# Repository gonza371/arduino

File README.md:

# Arduino Shields

Proyecto destinado a la creacion de Shields de Arduino con displays de 7 segmentos bajo distintos metodos. Proyecto CIII

## 🚀 Características

- Multiplexado de 3 displays de 7 segmentos.
- Controlado desde Arduino UNO usando solo el puerto D.
- Circuito en KiCad con transistores NPN (2N2219).
- Ideal para aprender manejo de displays en proyectos embebidos.

## 🛠 Requisitos

- Arduino UNO
- 3 Displays de 7 segmentos catodo común (HDSP-7401)
- Transistores 2N2219
- Resistencias de 330Ω (segmentos) y 1kΩ (base de transistores)
- Fuente de 5V (puede ser la del Arduino)

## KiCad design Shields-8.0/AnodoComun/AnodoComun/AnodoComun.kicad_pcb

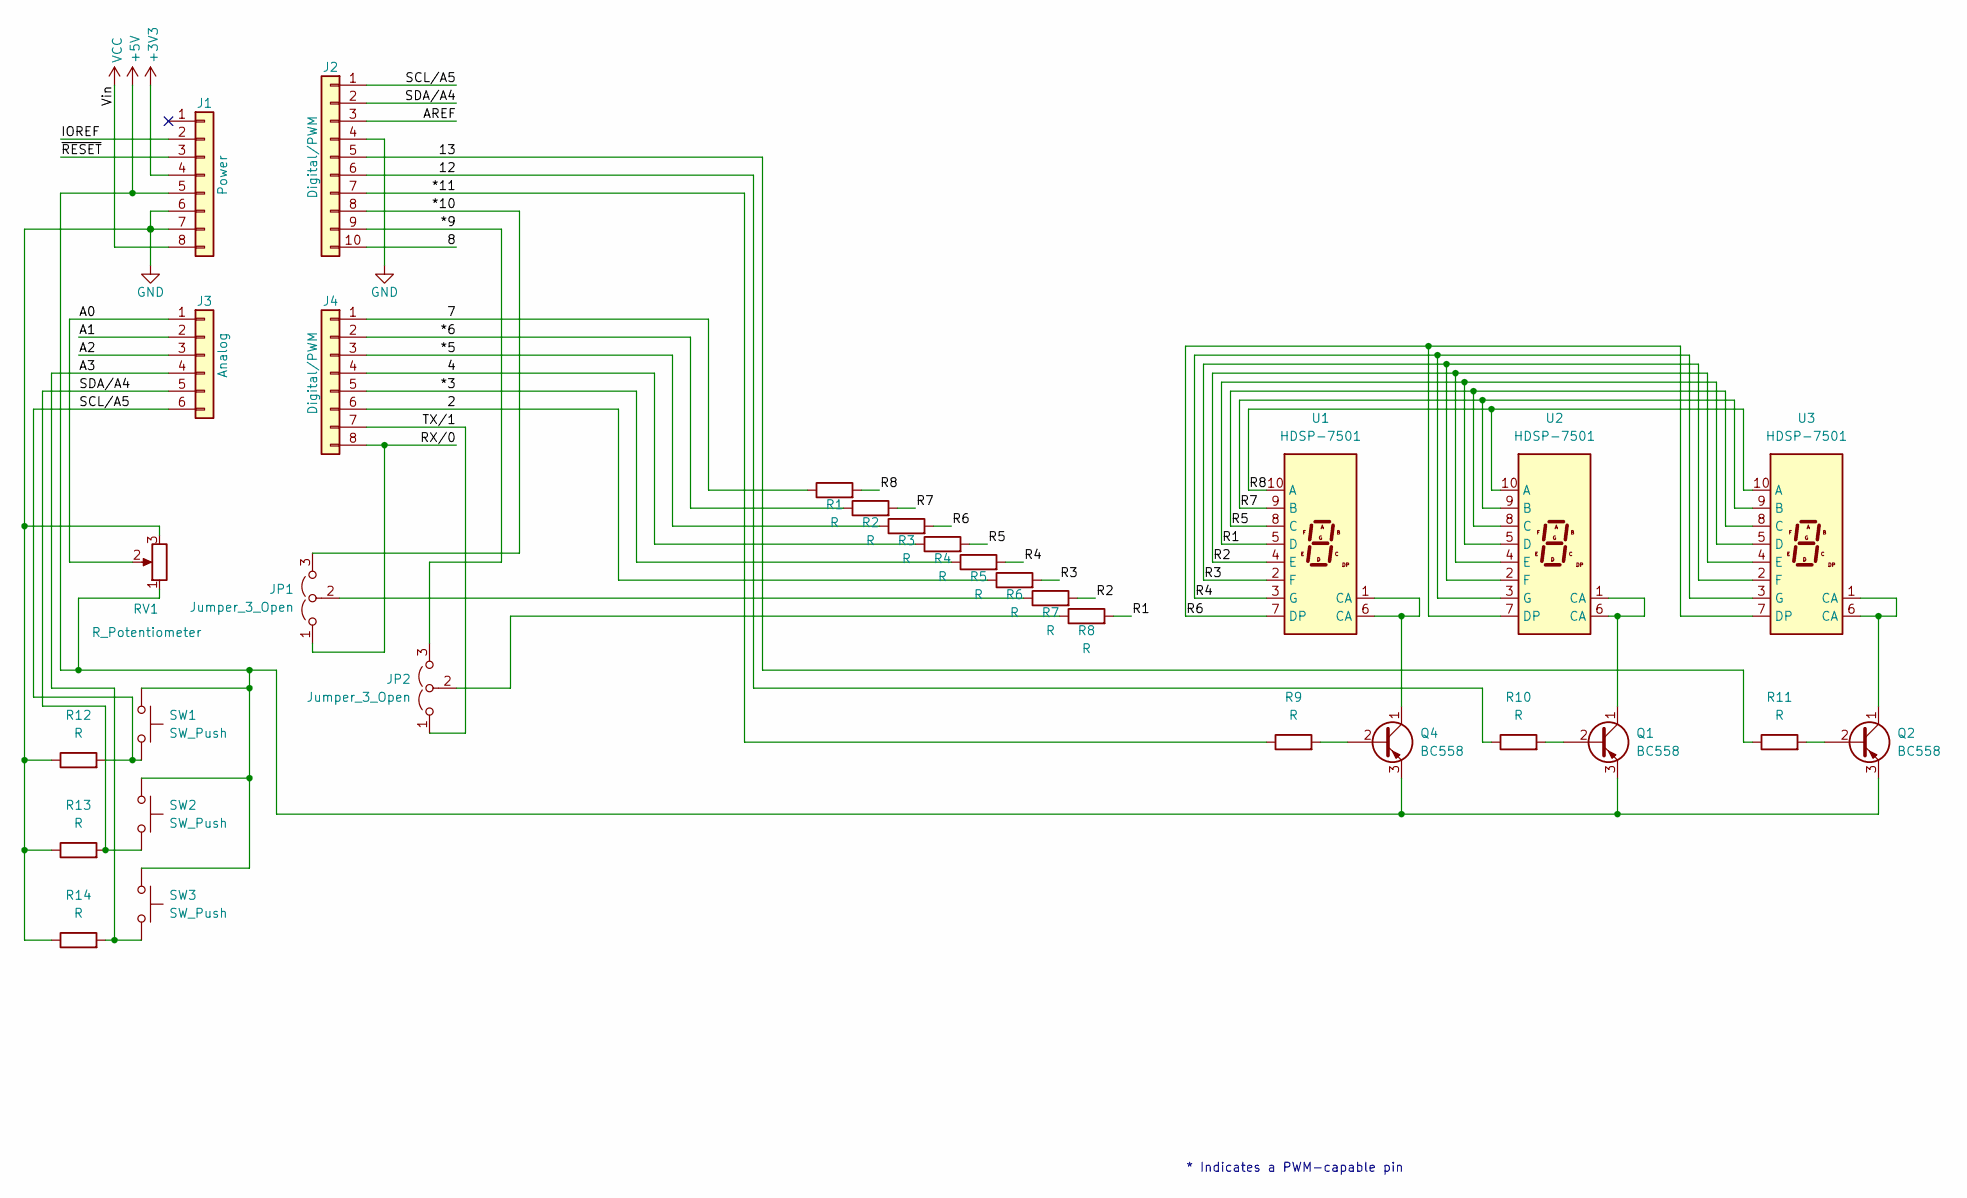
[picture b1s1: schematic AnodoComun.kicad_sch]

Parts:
J1: Power; PinSocket_1x08_P2.54mm_Vertical
J2: Digital/PWM; PinSocket_1x10_P2.54mm_Vertical
J3: Analog; PinSocket_1x06_P2.54mm_Vertical
J4: Digital/PWM; PinSocket_1x08_P2.54mm_Vertical
JP1, JP2: Jumper_3_Open; PinHeader_1x03_P2.54mm_Vertical
Q1, Q2, Q4: BC558; TO-92_Inline
R1, R2, R3, R4, R5, R6, R7, R8, R9, R10, R11, R12, R13, R14: R; R_Axial_DIN0207_L6.3mm_D2.5mm_P7.62mm_Horizontal
RV1: R_Potentiometer; Potentiometer_Alps_RK09K_Single_Horizontal
SW1, SW2, SW3: SW_Push; SW_PUSH_6mm_H4.3mm
U1, U2, U3: HDSP-7501; D1X8K_AC

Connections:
+3V3: J1.4
+5V: J1.5, Q1.3 (E), Q2.3 (E), Q4.3 (E), RV1.1, SW1.1, SW2.1, SW3.1
/2: J4.6, R6.1
/4: J4.4, R4.1
/7: J4.1, R1.1
/8: J2.10
/12: J2.6, R10.1
/13: J2.5, R11.1
/*3: J4.5, R5.1
/*5: J4.3, R3.1
/*6: J4.2, R2.1
/*9: J2.9, JP2.3 (B)
/*10: J2.8, JP1.3 (B)
/*11: J2.7, R9.1
/A0: J3.1, RV1.2
/A1: J3.2
/A2: J3.3
/A3: J3.4, R14.2, SW3.2
/AREF: J2.3
/IOREF: J1.2
/R1: R8.2, U1.5 (D), U2.5 (D), U3.5 (D)
/R2: R7.2, U1.4 (E), U2.4 (E), U3.4 (E)
/R3: R6.2, U1.2 (F), U2.2 (F), U3.2 (F)
/R4: R5.2, U1.3 (G), U2.3 (G), U3.3 (G)
/R5: R4.2, U1.8 (C), U2.8 (C), U3.8 (C)
/R6: R3.2, U1.7 (DP), U2.7 (DP), U3.7 (DP)
/R7: R2.2, U1.9 (B), U2.9 (B), U3.9 (B)
/R8: R1.2, U1.10 (A), U2.10 (A), U3.10 (A)
/RX/0: J4.8, JP1.1 (A)
/SCL/A5: J2.1, J3.6, R12.2, SW1.2
/SDA/A4: J2.2, J3.5, R13.2, SW2.2
/TX/1: J4.7, JP2.1 (A)
/~RESET: J1.3
GND: J1.6, J1.7, J2.4, R12.1, R13.1, R14.1, RV1.3
unnamed: JP1.2 (C), R7.1
unnamed: JP2.2 (C), R8.1
unnamed: Q1.2 (B), R10.2
unnamed: Q1.1 (C), U2.1 (CA), U2.6 (CA)
unnamed: Q2.2 (B), R11.2
unnamed: Q2.1 (C), U3.1 (CA), U3.6 (CA)
unnamed: Q4.2 (B), R9.2
unnamed: Q4.1 (C), U1.1 (CA), U1.6 (CA)
VCC: J1.8

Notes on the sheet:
* Indicates a PWM-capable pin

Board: 2 copper layers, 34 parts (0 on the bottom side), 35 nets, no tracks yet.

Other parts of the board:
MH1, MH2, MH3, MH4: MountingHole_3.2mm

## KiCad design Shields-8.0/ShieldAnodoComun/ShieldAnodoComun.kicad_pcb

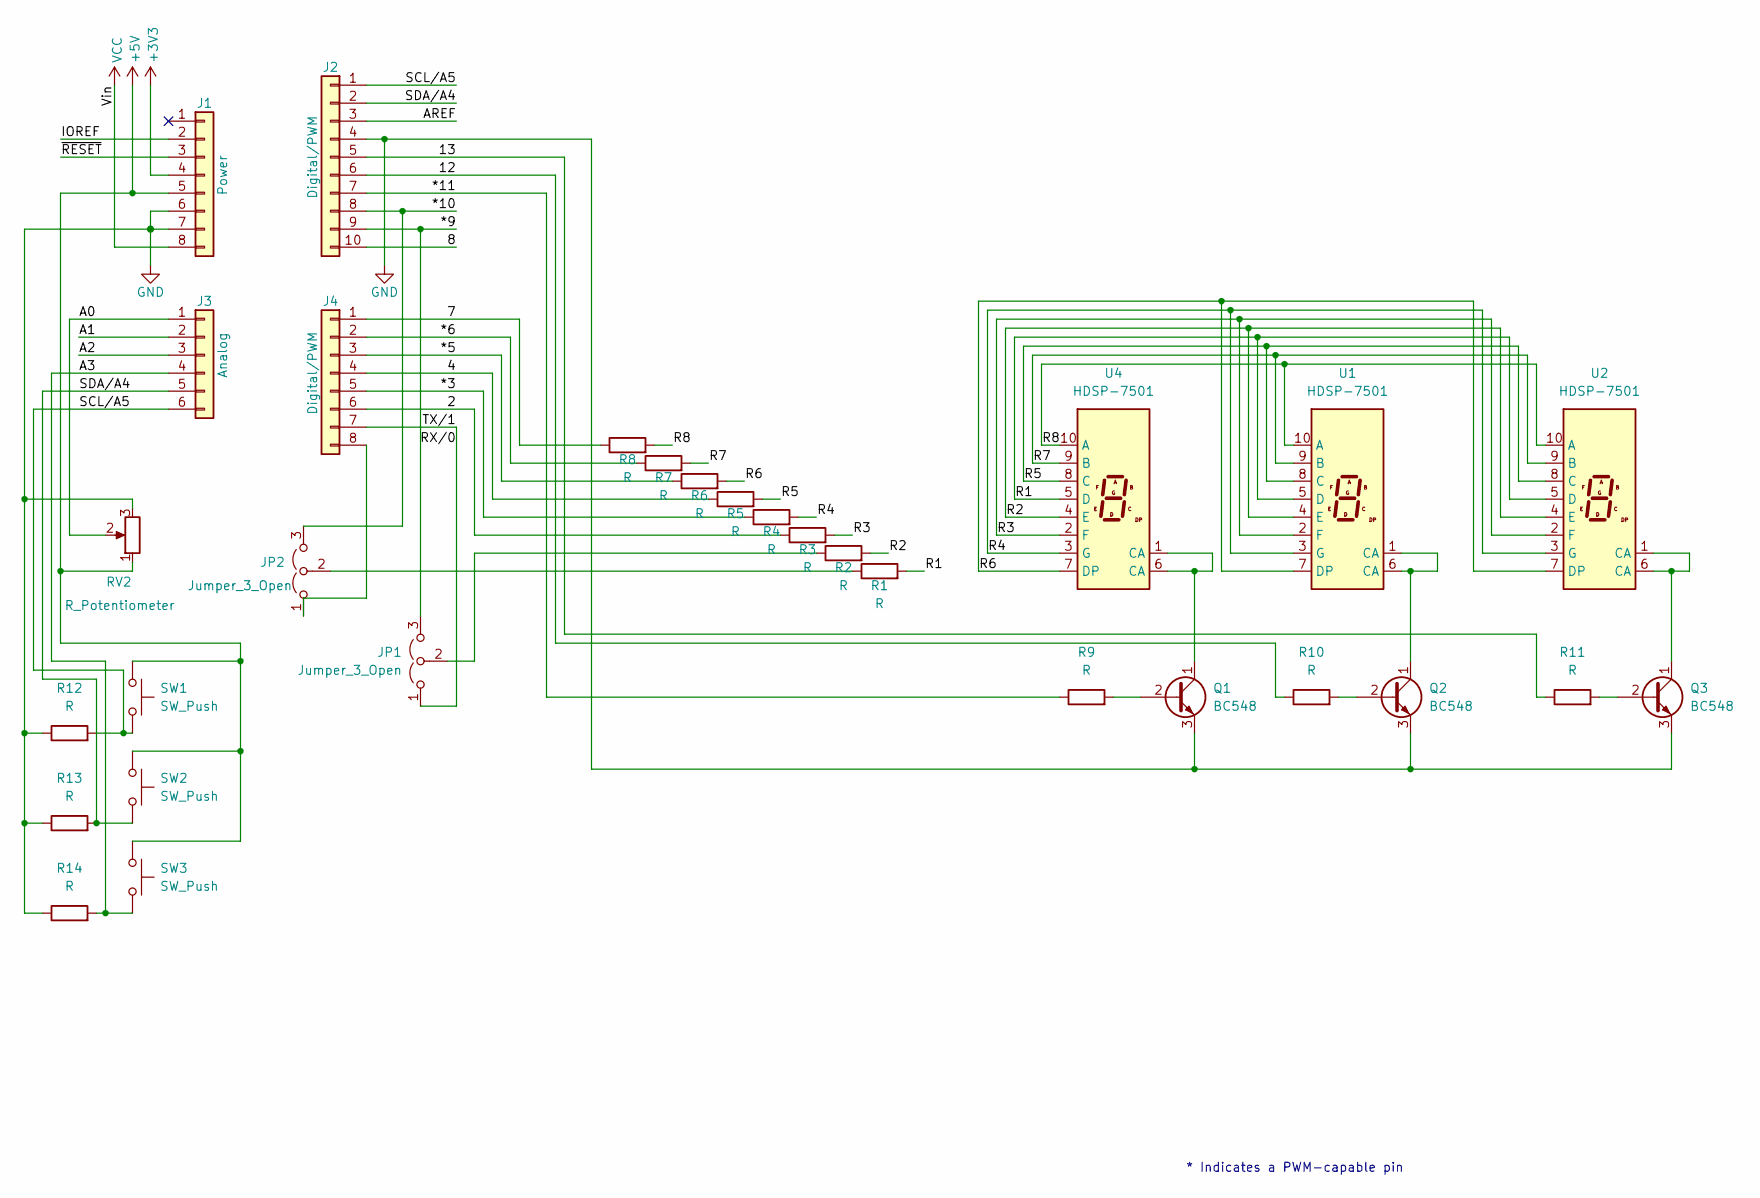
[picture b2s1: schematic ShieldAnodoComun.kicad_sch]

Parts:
J1: Power; PinSocket_1x08_P2.54mm_Vertical
J2: Digital/PWM; PinSocket_1x10_P2.54mm_Vertical
J3: Analog; PinSocket_1x06_P2.54mm_Vertical
J4: Digital/PWM; PinSocket_1x08_P2.54mm_Vertical
JP1, JP2: Jumper_3_Open; PinHeader_1x03_P2.54mm_Vertical
Q1, Q2, Q3: BC548; TO-92_Inline
R1, R2, R3, R4, R5, R6, R7, R8, R9, R10, R11, R12, R13, R14: R; R_Axial_DIN0207_L6.3mm_D2.5mm_P10.16mm_Horizontal
RV2: R_Potentiometer; Potentiometer_Alps_RK09K_Single_Horizontal
SW1, SW2, SW3: SW_Push; SW_PUSH_6mm_H4.3mm
U1, U2, U4: HDSP-7501; D1X8K-comun-medio

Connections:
+3V3: J1.4
+5V: J1.5, RV2.1, SW1.1, SW2.1, SW3.1
/2: J4.6, R3.1
/4: J4.4, R5.1
/7: J4.1, R8.1
/8: J2.10
/12: J2.6, R10.1
/13: J2.5, R11.1
/*3: J4.5, R4.1
/*5: J4.3, R6.1
/*6: J4.2, R7.1
/*9: J2.9, JP1.3 (B)
/*10: J2.8, JP2.3 (B)
/*11: J2.7, R9.1
/A0: J3.1, RV2.2
/A1: J3.2
/A2: J3.3
/A3: J3.4, R14.2, SW3.2
/AREF: J2.3
/IOREF: J1.2
/R1: R1.2, U1.5 (D), U2.5 (D), U4.5 (D)
/R2: R2.2, U1.4 (E), U2.4 (E), U4.4 (E)
/R3: R3.2, U1.2 (F), U2.2 (F), U4.2 (F)
/R4: R4.2, U1.3 (G), U2.3 (G), U4.3 (G)
/R5: R5.2, U1.8 (C), U2.8 (C), U4.8 (C)
/R6: R6.2, U1.7 (DP), U2.7 (DP), U4.7 (DP)
/R7: R7.2, U1.9 (B), U2.9 (B), U4.9 (B)
/R8: R8.2, U1.10 (A), U2.10 (A), U4.10 (A)
/RX/0: J4.7, JP1.1 (A)
/SCL/A5: J2.1, J3.6, R12.2, SW1.2
/SDA/A4: J2.2, J3.5, R13.2, SW2.2
/~RESET: J1.3
GND: J1.6, J1.7, J2.4, Q1.3 (E), Q2.3 (E), Q3.3 (E), R12.1, R13.1, R14.1, RV2.3
unnamed: J4.8, JP2.1 (A)
unnamed: JP1.2 (C), R2.1
unnamed: JP2.2 (C), R1.1
unnamed: Q1.2 (B), R9.2
unnamed: Q1.1 (C), U4.1 (CA), U4.6 (CA)
unnamed: Q2.2 (B), R10.2
unnamed: Q2.1 (C), U1.1 (CA), U1.6 (CA)
unnamed: Q3.2 (B), R11.2
unnamed: Q3.1 (C), U2.1 (CA), U2.6 (CA)
VCC: J1.8

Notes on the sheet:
* Indicates a PWM-capable pin

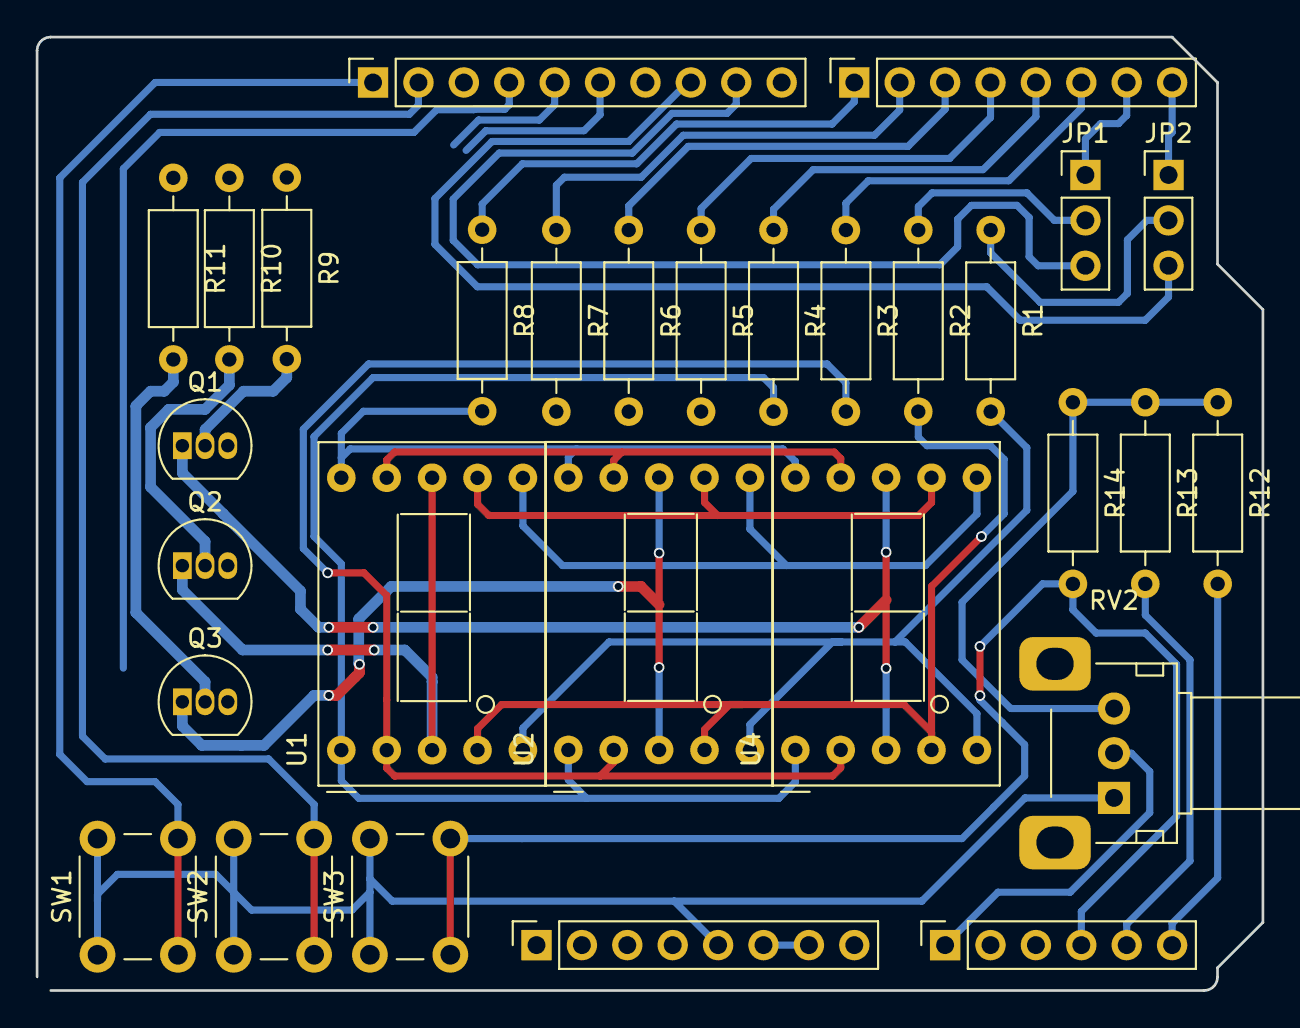
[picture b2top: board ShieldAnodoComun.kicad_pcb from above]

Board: 2 copper layers, 68.6 x 53.3 mm, 30 parts (0 on the bottom side), 35 nets.

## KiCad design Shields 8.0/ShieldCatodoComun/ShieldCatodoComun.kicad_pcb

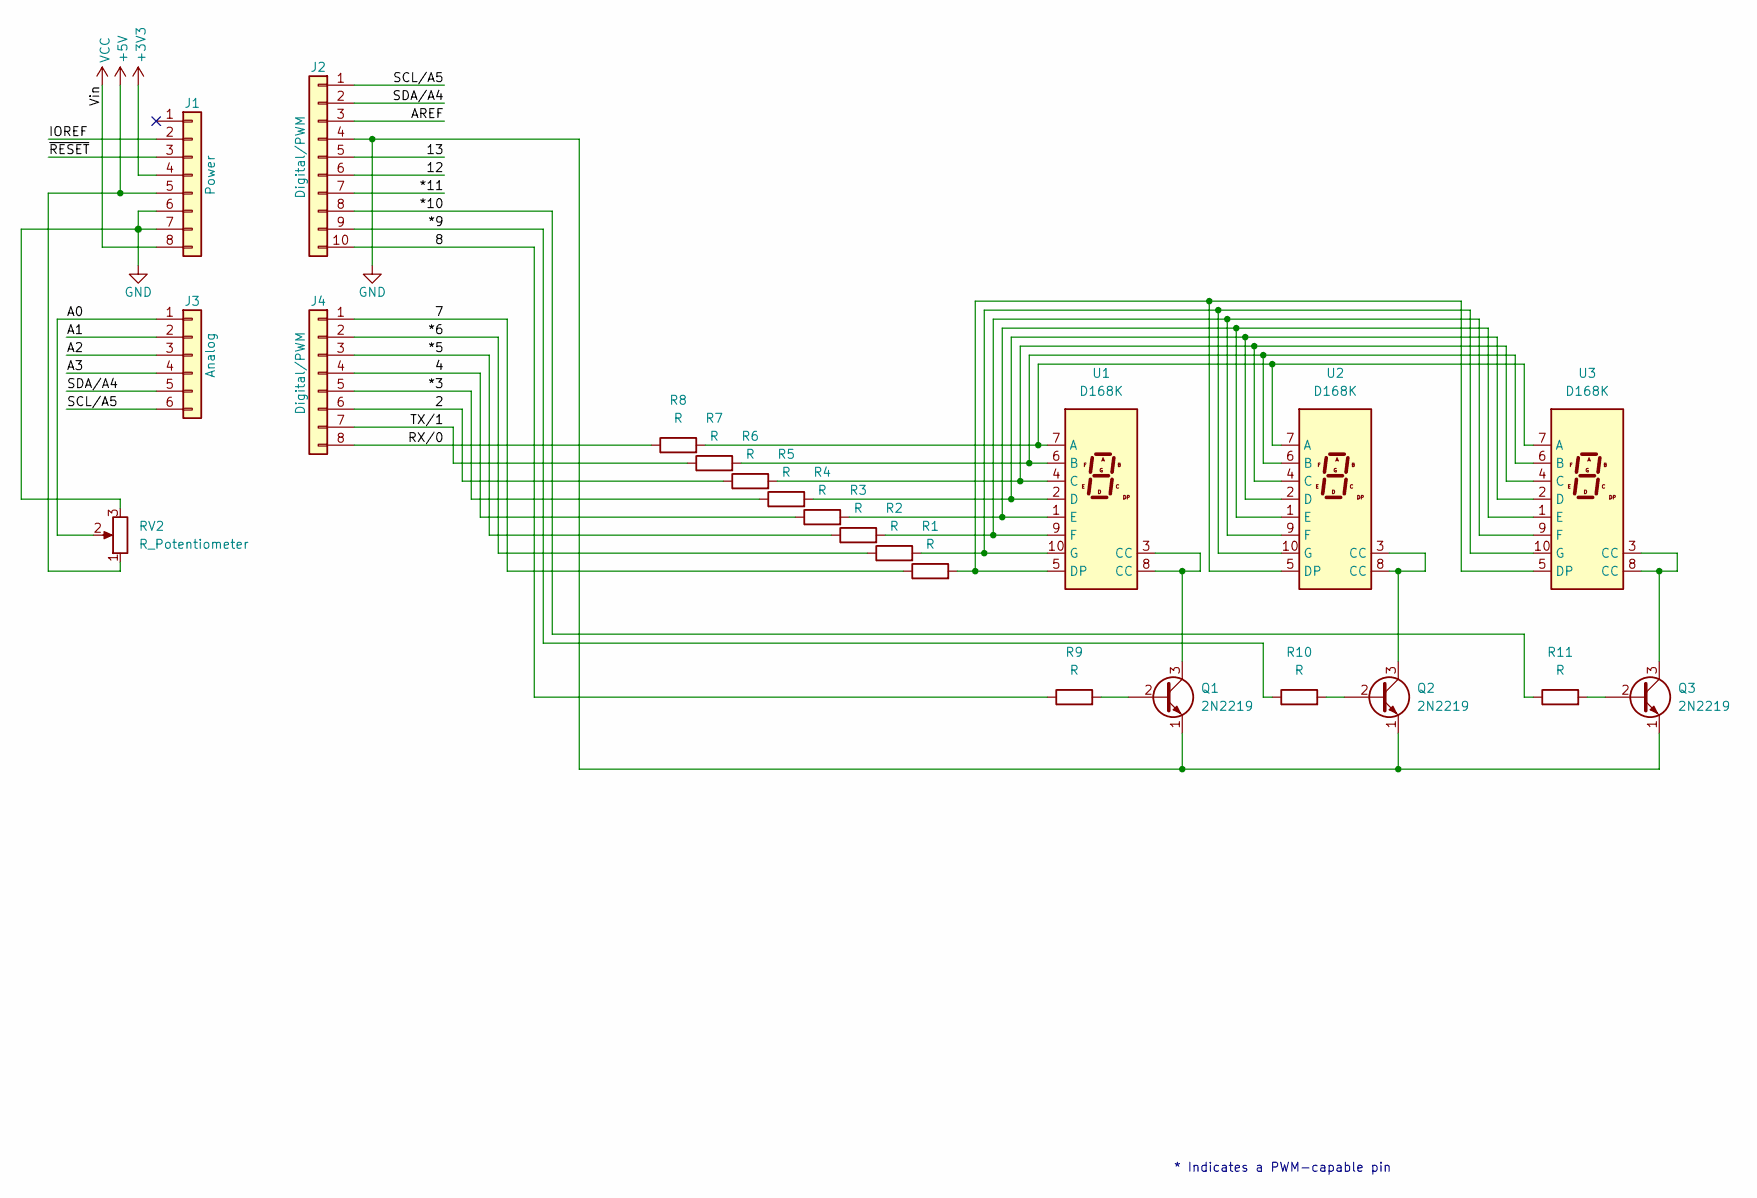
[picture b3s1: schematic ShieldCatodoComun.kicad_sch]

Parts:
J1: Power; PinSocket_1x08_P2.54mm_Vertical
J2: Digital/PWM; PinSocket_1x10_P2.54mm_Vertical
J3: Analog; PinSocket_1x06_P2.54mm_Vertical
J4: Digital/PWM; PinSocket_1x08_P2.54mm_Vertical
Q1, Q2, Q3: 2N2219; TO-39-3
R1, R2, R3, R4, R5, R6, R7, R8, R9, R10, R11: R; R_Axial_DIN0207_L6.3mm_D2.5mm_P10.16mm_Horizontal
RV2: R_Potentiometer; Potentiometer_Alpha_RD901F-40-00D_Single_Vertical
U1, U2, U3: D168K; D1X8K

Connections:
+3V3: J1.4
+5V: J1.5, RV2.1
/2: J4.6, R6.1
/4: J4.4, R4.1
/7: J4.1, R1.1
/8: J2.10, R9.1
/12: J2.6
/13: J2.5
/*3: J4.5, R5.1
/*5: J4.3, R3.1
/*6: J4.2, R2.1
/*9: J2.9, R10.1
/*10: J2.8, R11.1
/*11: J2.7
/A0: J3.1, RV2.2
/A1: J3.2
/A2: J3.3
/A3: J3.4
/AREF: J2.3
/IOREF: J1.2
/RX/0: J4.8, R8.1
/SCL/A5: J2.1, J3.6
/SDA/A4: J2.2, J3.5
/TX/1: J4.7, R7.1
/~RESET: J1.3
GND: J1.6, J1.7, J2.4, Q1.1 (E), Q2.1 (E), Q3.1 (E), RV2.3
unnamed: Q1.2 (B), R9.2
unnamed: Q1.3 (C), U1.3 (CC), U1.8 (CC)
unnamed: Q2.2 (B), R10.2
unnamed: Q2.3 (C), U2.3 (CC), U2.8 (CC)
unnamed: Q3.2 (B), R11.2
unnamed: Q3.3 (C), U3.3 (CC), U3.8 (CC)
unnamed: R8.2, U1.7 (A), U2.7 (A), U3.7 (A)
unnamed: R7.2, U1.6 (B), U2.6 (B), U3.6 (B)
unnamed: R6.2, U1.4 (C), U2.4 (C), U3.4 (C)
unnamed: R5.2, U1.2 (D), U2.2 (D), U3.2 (D)
unnamed: R1.2, U1.5 (DP), U2.5 (DP), U3.5 (DP)
unnamed: R4.2, U1.1 (E), U2.1 (E), U3.1 (E)
unnamed: R3.2, U1.9 (F), U2.9 (F), U3.9 (F)
unnamed: R2.2, U1.10 (G), U2.10 (G), U3.10 (G)
VCC: J1.8

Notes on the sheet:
* Indicates a PWM-capable pin

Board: 2 copper layers, 26 parts (0 on the bottom side), 30 nets, no tracks yet.

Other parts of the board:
MH1, MH2, MH3, MH4: MountingHole_3.2mm

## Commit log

2025-04-13 Primer Commit
2025-04-13 Actualizacion README
2025-04-13 Adicion Esquematico de Anodo Comun
2025-04-24 Proyecto Kicad para Anodo Común
2025-04-24 Ordenando
2025-04-28 Añadiendo proyecto kicad8.0 Catodo Común
2025-04-28 Implementacion del PCB
2025-04-28 Agregado de jumpers
2025-04-29 Arreglos menores
2025-05-01 Esquematico completo y primeros enrutados
2025-05-07 Eliminada carpeta duplicada
2025-05-08 Arreglos para enrutar
2025-05-09 Continuacion de enrutados
2025-05-15 Adicion de esquematicos finales para Anodo comun y Catodo comun
